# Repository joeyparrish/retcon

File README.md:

# Retro Console Controller

Use comfortable wireless PS3 controllers on your old Sega or Nintendo system.

> :warning: **NOTE** :warning:: _**This project has been deprecated.**_
> 
> I bought receivers from 8bitdo that do much more than my homebrew project ever could, in a smaller space, for less money.
> For example, here you can get a Sega Genesis receiver for bluetooth controllers that is tiny and powered by the Sega itself: https://www.8bitdo.com/retro-receiver-genesis-mega-drive/
> 
> I had begun a redesign based on a microcontroller that I hoped would be powered by the console itself, and would use generic Bluetooth instead of PS3, but for $20 (as of Feb 2024) it's hard to beat what 8bitdo is doing.
> 
> Feel free to build off of this repo if you wish, but I'm abandoning it in favor of https://www.8bitdo.com/
> 
> -Joey

-----

The PS3 controllers pair with a Raspberry Pi, which translates the controller
inputs to the game console through an external circuit.

[The repository][] hosts the schematics, board layouts, and source code.

For a list of known issues, see our [issue tracker][].

[The repository]: https://github.com/cashpipeplusplus/retcon
[issue tracker]: https://github.com/cashpipeplusplus/retcon/issues

## Software

RetCon consists of three pieces of software that run on a Raspberry Pi:

 * retcon - reads events from the gamepad and toggle GPIO pins
 * trusting-steed - waits for gamepads and marks them as "trusted"
 * sixpair - waits for PS3 controllers over USB and pairs them for bluetooth

These run on the Raspberry Pi, and I do not recommend cross-compiling them.
To build them, check out the source on Raspbian, install the deps, then build
the debian package:

```sh
git clone https://github.com/cashpipeplusplus/retcon
sudo apt-get install libusb-dev pigpio python-gobject python-dbus
cd retcon/src/
fakeroot ./debian/rules binary
```

To install on Raspbian:

```sh
sudo dpkg -i ../retcon_0.0.1-1_armhf.deb
```

## Raspberry Pi SD card image

The SD card image is generated using a fork of a tool called pi-gen, which is
included as a submodule.

From retcon, you can check out the pi-gen code like this:

```sh
git submodule update --init --recursive
```

To build the SD image, first you must build the retcon debian package from
Raspbian.  Then, copy the deb file to your Linux machine and build the SD image
there.  Assuming the deb file is in the retcon folder, run this:

```sh
cd pi-gen
sudo ./build.sh ../retcon_0.0.1-1_armhf.deb
```

The output will appear in `deploy/`.

## Pre-built SD card image

Pre-built SD card images are available from the [releases][] page.

[releases]: https://github.com/cashpipeplusplus/retcon/releases

## Hardware

The Raspberry Pi communicates with the game console through an external
circuit.  Schematics and board layouts for this extra hardware can be found
in the `circuit/` folder.  The board file can be uploaded directly to
[DirtyPCBs][] if you want the boards printed for you.  More details can be
found in `circuit/README.md`.

[DirtyPCBs]: http://dirtypcbs.com/

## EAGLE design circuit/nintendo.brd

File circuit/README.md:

These are the schematic and board files for the external circuit part of the
project.  This circuit is driven by the Raspberry Pi and translates GPIO pins
to the game console.

These files were created with the free version of [Eagle][] v7.7.0.

 - sega.sch (Eagle Schematic)
 - sega.sch.1.png (screenshot of the schematic)
 - sega.sch.2.png (screenshot of the schematic)
 - sega.brd (Eagle Board)
 - sega.brd.png (screenshot of the board)

The board file can be uploaded directly to [DirtyPCBs][] to be printed.

[Eagle]: https://cadsoft.io/
[DirtyPCBs]: http://dirtypcbs.com/

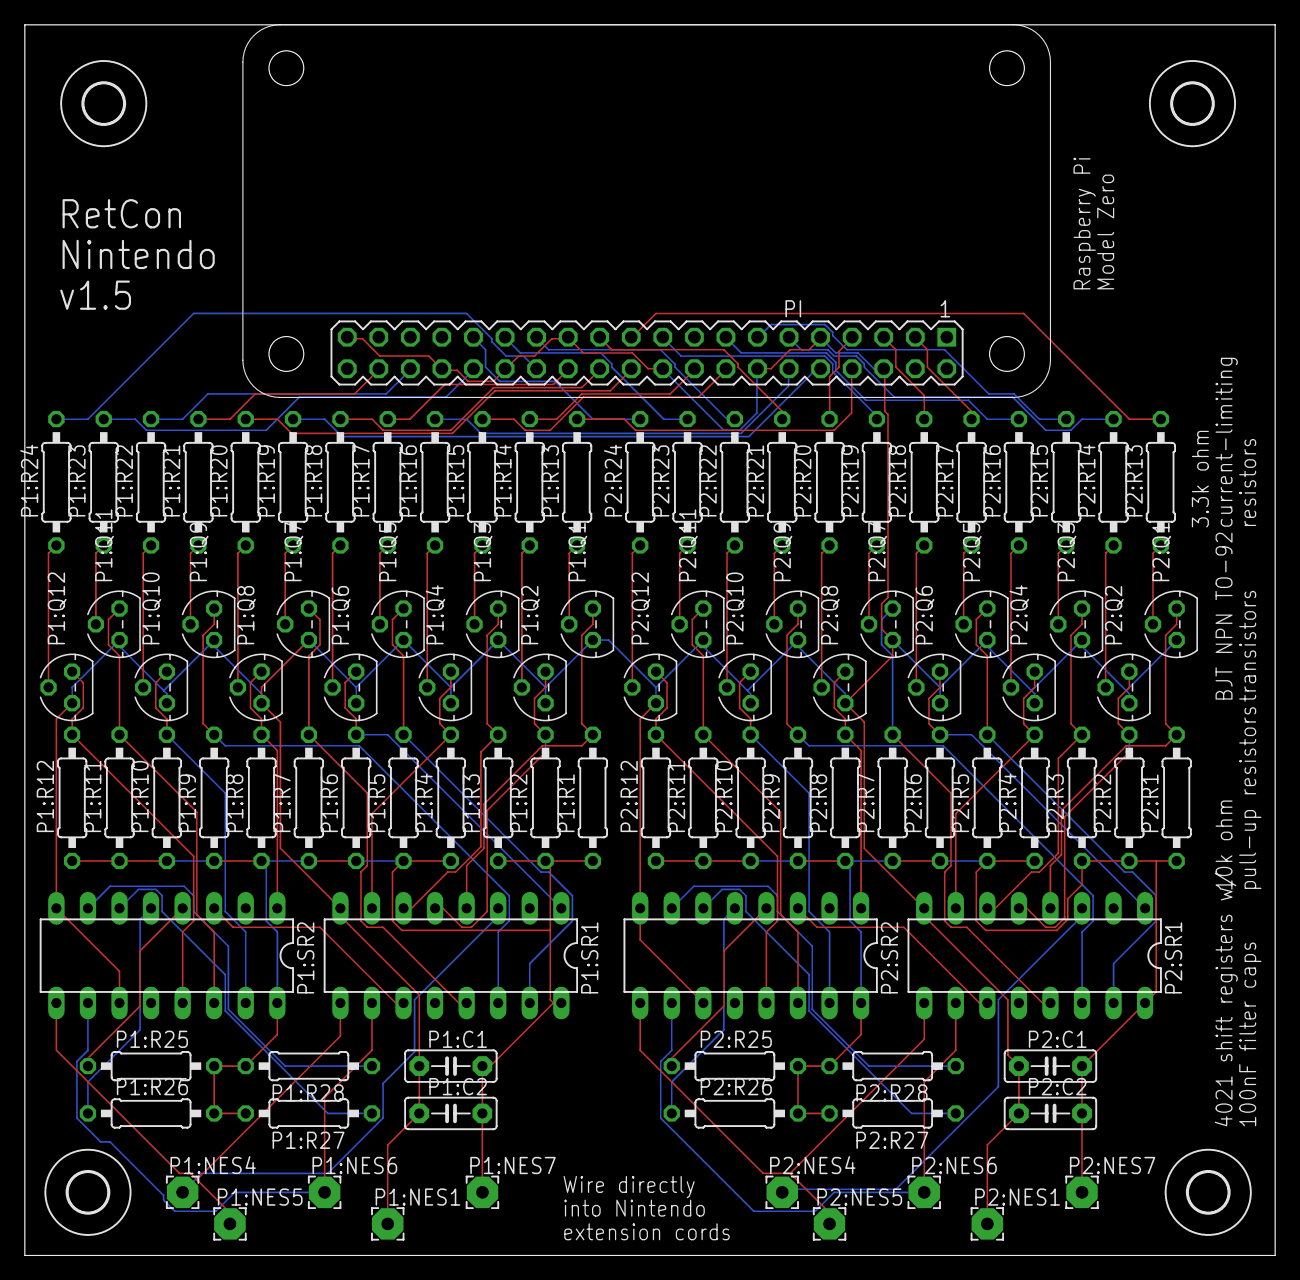
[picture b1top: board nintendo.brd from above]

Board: 2 copper layers, 100.6 x 99.0 mm, 103 parts (0 on the bottom side), 91 nets.

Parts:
P1:C1, P1:C2, P2:C1, P2:C2: 100nF; C5B2.5
P1:NES1, P1:NES4, P1:NES5, P1:NES6, P1:NES7, P2:NES1, P2:NES4, P2:NES5, P2:NES6, P2:NES7: -; 2,54/1,0
P1:Q1, P1:Q2, P1:Q3, P1:Q4, P1:Q5, P1:Q6, P1:Q7, P1:Q8, P1:Q9, P1:Q10, P1:Q11, P1:Q12, P2:Q1, P2:Q2, P2:Q3, P2:Q4, P2:Q5, P2:Q6, P2:Q7, P2:Q8, P2:Q9, P2:Q10, P2:Q11, P2:Q12: 2N3904; TO92
P1:R1, P1:R2, P1:R3, P1:R4, P1:R5, P1:R6, P1:R7, P1:R8, P1:R9, P1:R10, P1:R11, P1:R12, P1:R25, P1:R26, P1:R27, P1:R28, P2:R1, P2:R2, P2:R3, P2:R4, P2:R5, P2:R6, P2:R7, P2:R8, P2:R9, P2:R10, P2:R11, P2:R12, P2:R25, P2:R26, P2:R27, P2:R28: 10k; 0207/10
P1:R13, P1:R14, P1:R15, P1:R16, P1:R17, P1:R18, P1:R19, P1:R20, P1:R21, P1:R22, P1:R23, P1:R24, P2:R13, P2:R14, P2:R15, P2:R16, P2:R17, P2:R18, P2:R19, P2:R20, P2:R21, P2:R22, P2:R23, P2:R24: 3.3k; 0207/10
P1:SR1, P1:SR2, P2:SR1, P2:SR2: 4021N; DIL16
PI: PIZERO_THROUGH_HOLE; PIZERO_THOUGH_HOLE
U$1, U$2, U$3, U$4: 3,2

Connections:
unnamed: P2:R14.2, PI.11
unnamed: P1:C1.1, P1:C2.1, P1:NES1.1, P1:Q1.3, P1:Q2.3, P1:Q3.3, P1:Q4.3, P1:Q5.3, P1:Q6.3, P1:Q7.3, P1:Q8.3, P1:Q9.3, P1:Q10.3, P1:Q11.3, P1:Q12.3, P1:SR1.8, P1:SR2.8, P1:SR2.11, P2:C1.1, P2:C2.1, P2:NES1.1, P2:Q1.3, P2:Q2.3, P2:Q3.3, P2:Q4.3, P2:Q5.3, P2:Q6.3, P2:Q7.3, P2:Q8.3, P2:Q9.3, P2:Q10.3, P2:Q11.3, P2:Q12.3, P2:SR1.8, P2:SR2.8, P2:SR2.11, PI.6, PI.9, PI.14, PI.20, PI.25, PI.30, PI.34, PI.39
unnamed: P2:R15.2, PI.13
unnamed: P2:R17.2, PI.3
unnamed: P2:R18.2, PI.5
unnamed: P2:R20.2, PI.7
unnamed: P2:R16.2, PI.15
unnamed: P2:R19.2, PI.19
unnamed: P2:R13.2, PI.21
unnamed: P1:R13.2, PI.8
unnamed: P1:R19.2, PI.10
unnamed: P1:R16.2, PI.12
unnamed: P1:R15.2, PI.16
unnamed: P1:R14.2, PI.18
unnamed: P1:R20.2, PI.22
unnamed: P1:R18.2, PI.24
unnamed: P1:R17.2, PI.26
unnamed: P2:R21.2, PI.23
unnamed: P2:R22.2, PI.27
unnamed: P2:R23.2, PI.29
unnamed: P2:R24.2, PI.31
unnamed: P1:R21.2, PI.38
unnamed: P1:R22.2, PI.36
unnamed: P1:R23.2, PI.32
unnamed: P1:R24.2, PI.28
P1:A: P1:Q5.1, P1:R5.2, P1:SR1.15
P1:B: P1:Q6.1, P1:R6.2, P1:SR1.1
P1:C: P1:Q8.1, P1:R8.2, P1:SR2.1
P1:CLK: P1:NES6.1, P1:SR1.10, P1:SR2.10
P1:D: P1:Q2.1, P1:R2.2, P1:SR1.5
P1:L: P1:Q3.1, P1:R3.2, P1:SR1.6
P1:LATCH: P1:NES5.1, P1:SR1.9, P1:SR2.9
P1:N$1: P1:Q9.2, P1:R21.1
P1:N$2: P1:Q1.2, P1:R13.1
P1:N$3: P1:Q10.2, P1:R22.1
P1:N$4: P1:Q11.2, P1:R23.1
P1:N$5: P1:Q12.2, P1:R24.1
P1:N$9: P1:Q2.2, P1:R14.1
P1:N$10: P1:Q3.2, P1:R15.1
P1:N$11: P1:Q4.2, P1:R16.1
P1:N$12: P1:Q5.2, P1:R17.1
P1:N$13: P1:Q6.2, P1:R18.1
P1:N$14: P1:Q7.2, P1:R19.1
P1:N$15: P1:Q8.2, P1:R20.1
P1:N$19: P1:SR1.11, P1:SR2.3
P1:N$20: P1:R25.1, P1:SR2.4
P1:N$21: P1:R26.1, P1:SR2.5
P1:N$22: P1:R27.1, P1:SR2.6
P1:N$23: P1:R28.1, P1:SR2.7
P1:OUT: P1:NES4.1, P1:SR1.3
P1:R: P1:Q4.1, P1:R4.2, P1:SR1.7
P1:SL: P1:Q9.1, P1:R9.2, P1:SR1.14
P1:ST: P1:Q7.1, P1:R7.2, P1:SR1.13
P1:TL: P1:Q11.1, P1:R11.2, P1:SR2.14
P1:TR: P1:Q12.1, P1:R12.2, P1:SR2.13
P1:U: P1:Q1.1, P1:R1.2, P1:SR1.4
P1:VCC: P1:C1.2, P1:C2.2, P1:NES7.1, P1:R1.1, P1:R2.1, P1:R3.1, P1:R4.1, P1:R5.1, P1:R6.1, P1:R7.1, P1:R8.1, P1:R9.1, P1:R10.1, P1:R11.1, P1:R12.1, P1:R25.2, P1:R26.2, P1:R27.2, P1:R28.2, P1:SR1.16, P1:SR2.16
P1:X: P1:Q10.1, P1:R10.2, P1:SR2.15
P2:A: P2:Q5.1, P2:R5.2, P2:SR1.15
P2:B: P2:Q6.1, P2:R6.2, P2:SR1.1
P2:C: P2:Q8.1, P2:R8.2, P2:SR2.1
P2:CLK: P2:NES6.1, P2:SR1.10, P2:SR2.10
P2:D: P2:Q2.1, P2:R2.2, P2:SR1.5
P2:L: P2:Q3.1, P2:R3.2, P2:SR1.6
P2:LATCH: P2:NES5.1, P2:SR1.9, P2:SR2.9
P2:N$1: P2:Q9.2, P2:R21.1
P2:N$2: P2:Q1.2, P2:R13.1
P2:N$3: P2:Q10.2, P2:R22.1
P2:N$4: P2:Q11.2, P2:R23.1
P2:N$5: P2:Q12.2, P2:R24.1
P2:N$9: P2:Q2.2, P2:R14.1
P2:N$10: P2:Q3.2, P2:R15.1
P2:N$11: P2:Q4.2, P2:R16.1
P2:N$12: P2:Q5.2, P2:R17.1
P2:N$13: P2:Q6.2, P2:R18.1
P2:N$14: P2:Q7.2, P2:R19.1
P2:N$15: P2:Q8.2, P2:R20.1
P2:N$19: P2:SR1.11, P2:SR2.3
P2:N$20: P2:R25.1, P2:SR2.4
P2:N$21: P2:R26.1, P2:SR2.5
P2:N$22: P2:R27.1, P2:SR2.6
P2:N$23: P2:R28.1, P2:SR2.7
P2:OUT: P2:NES4.1, P2:SR1.3
P2:R: P2:Q4.1, P2:R4.2, P2:SR1.7
P2:SL: P2:Q9.1, P2:R9.2, P2:SR1.14
P2:ST: P2:Q7.1, P2:R7.2, P2:SR1.13
P2:TL: P2:Q11.1, P2:R11.2, P2:SR2.14
P2:TR: P2:Q12.1, P2:R12.2, P2:SR2.13
P2:U: P2:Q1.1, P2:R1.2, P2:SR1.4
P2:VCC: P2:C1.2, P2:C2.2, P2:NES7.1, P2:R1.1, P2:R2.1, P2:R3.1, P2:R4.1, P2:R5.1, P2:R6.1, P2:R7.1, P2:R8.1, P2:R9.1, P2:R10.1, P2:R11.1, P2:R12.1, P2:R25.2, P2:R26.2, P2:R27.2, P2:R28.2, P2:SR1.16, P2:SR2.16
P2:X: P2:Q10.1, P2:R10.2, P2:SR2.15

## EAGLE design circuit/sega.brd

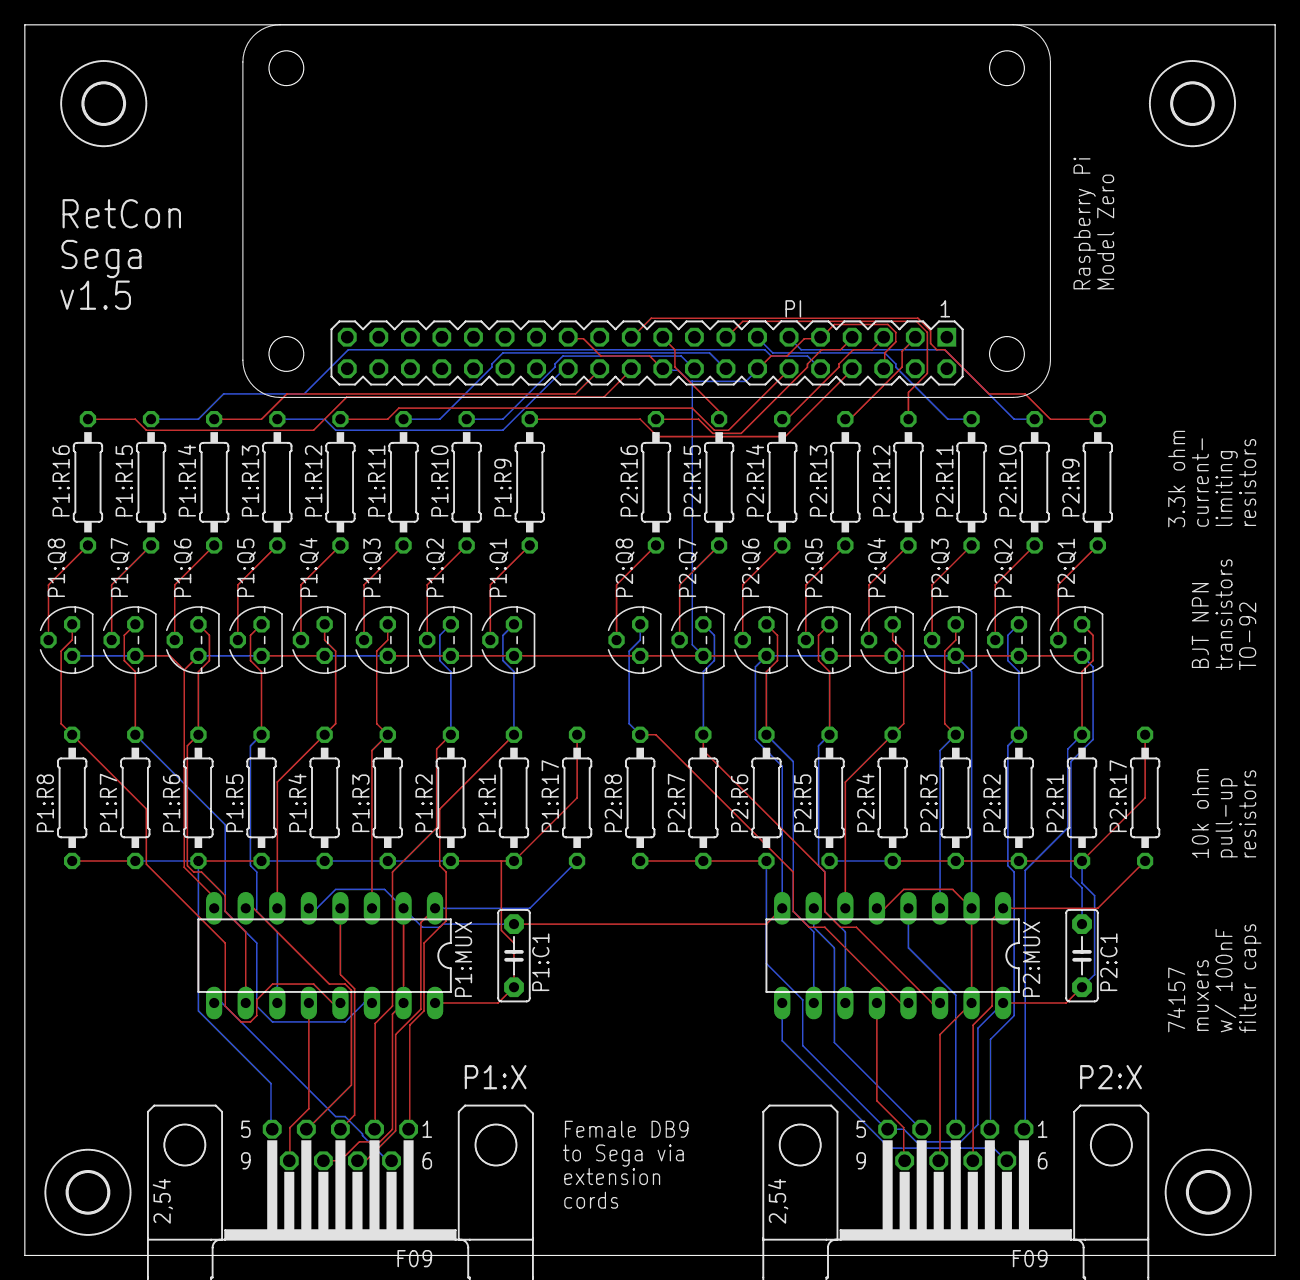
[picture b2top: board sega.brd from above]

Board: 2 copper layers, 100.6 x 99.0 mm, 61 parts (0 on the bottom side), 61 nets.

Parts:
P1:C1, P2:C1: 100nF; C5B2.5
P1:MUX, P2:MUX: 74LS157N; DIL16
P1:Q1, P1:Q2, P1:Q3, P1:Q4, P1:Q5, P1:Q6, P1:Q7, P1:Q8, P2:Q1, P2:Q2, P2:Q3, P2:Q4, P2:Q5, P2:Q6, P2:Q7, P2:Q8: 2N3904; TO92
P1:R1, P1:R2, P1:R3, P1:R4, P1:R5, P1:R6, P1:R7, P1:R8, P1:R17, P2:R1, P2:R2, P2:R3, P2:R4, P2:R5, P2:R6, P2:R7, P2:R8, P2:R17: 10k; 0207/10
P1:R9, P1:R10, P1:R11, P1:R12, P1:R13, P1:R14, P1:R15, P1:R16, P2:R9, P2:R10, P2:R11, P2:R12, P2:R13, P2:R14, P2:R15, P2:R16: 3.3k; 0207/10
P1:X, P2:X: -; F09H
PI: PIZERO_THROUGH_HOLE; PIZERO_THOUGH_HOLE
U$1, U$2, U$3, U$4: 3,2

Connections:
GND: P1:C1.1, P1:MUX.2, P1:MUX.5, P1:MUX.8, P1:MUX.15, P1:Q1.3, P1:Q2.3, P1:Q3.3, P1:Q4.3, P1:Q5.3, P1:Q6.3, P1:Q7.3, P1:Q8.3, P1:X.8, P2:C1.1, P2:MUX.2, P2:MUX.5, P2:MUX.8, P2:MUX.15, P2:Q1.3, P2:Q2.3, P2:Q3.3, P2:Q4.3, P2:Q5.3, P2:Q6.3, P2:Q7.3, P2:Q8.3, P2:X.8, PI.6, PI.9, PI.14, PI.20, PI.25
unnamed: P2:R10.2, PI.11
unnamed: P2:R11.2, PI.13
unnamed: P2:R13.2, PI.3
unnamed: P2:R14.2, PI.5
unnamed: P2:R16.2, PI.7
unnamed: P2:R12.2, PI.15
unnamed: P2:R15.2, PI.19
unnamed: P2:R9.2, PI.21
unnamed: P1:R9.2, PI.8
unnamed: P1:R15.2, PI.10
unnamed: P1:R12.2, PI.12
unnamed: P1:R11.2, PI.16
unnamed: P1:R10.2, PI.18
unnamed: P1:R16.2, PI.22
unnamed: P1:R14.2, PI.24
unnamed: P1:R13.2, PI.26
P1:A: P1:MUX.11, P1:Q5.1, P1:R5.2
P1:A|B: P1:MUX.9, P1:X.6
P1:B: P1:MUX.10, P1:Q6.1, P1:R6.2
P1:C: P1:MUX.13, P1:Q8.1, P1:R8.2
P1:D: P1:Q2.1, P1:R2.2, P1:X.2
P1:G|L: P1:MUX.4, P1:X.3
P1:G|R: P1:MUX.7, P1:X.4
P1:L: P1:MUX.3, P1:Q3.1, P1:R3.2
P1:N$2: P1:Q1.2, P1:R9.1
P1:N$9: P1:Q2.2, P1:R10.1
P1:N$10: P1:Q3.2, P1:R11.1
P1:N$11: P1:Q4.2, P1:R12.1
P1:N$12: P1:Q5.2, P1:R13.1
P1:N$13: P1:Q6.2, P1:R14.1
P1:N$14: P1:Q7.2, P1:R15.1
P1:N$15: P1:Q8.2, P1:R16.1
P1:R: P1:MUX.6, P1:Q4.1, P1:R4.2
P1:S: P1:MUX.14, P1:Q7.1, P1:R7.2
P1:SEL: P1:MUX.1, P1:R17.1, P1:X.7
P1:S|C: P1:MUX.12, P1:X.9
P1:U: P1:Q1.1, P1:R1.2, P1:X.1
P1:VCC: P1:C1.2, P1:MUX.16, P1:R1.1, P1:R2.1, P1:R3.1, P1:R4.1, P1:R5.1, P1:R6.1, P1:R7.1, P1:R8.1, P1:R17.2, P1:X.5
P2:A: P2:MUX.11, P2:Q5.1, P2:R5.2
P2:A|B: P2:MUX.9, P2:X.6
P2:B: P2:MUX.10, P2:Q6.1, P2:R6.2
P2:C: P2:MUX.13, P2:Q8.1, P2:R8.2
P2:D: P2:Q2.1, P2:R2.2, P2:X.2
P2:G|L: P2:MUX.4, P2:X.3
P2:G|R: P2:MUX.7, P2:X.4
P2:L: P2:MUX.3, P2:Q3.1, P2:R3.2
P2:N$2: P2:Q1.2, P2:R9.1
P2:N$9: P2:Q2.2, P2:R10.1
P2:N$10: P2:Q3.2, P2:R11.1
P2:N$11: P2:Q4.2, P2:R12.1
P2:N$12: P2:Q5.2, P2:R13.1
P2:N$13: P2:Q6.2, P2:R14.1
P2:N$14: P2:Q7.2, P2:R15.1
P2:N$15: P2:Q8.2, P2:R16.1
P2:R: P2:MUX.6, P2:Q4.1, P2:R4.2
P2:S: P2:MUX.14, P2:Q7.1, P2:R7.2
P2:SEL: P2:MUX.1, P2:R17.1, P2:X.7
P2:S|C: P2:MUX.12, P2:X.9
P2:U: P2:Q1.1, P2:R1.2, P2:X.1
P2:VCC: P2:C1.2, P2:MUX.16, P2:R1.1, P2:R2.1, P2:R3.1, P2:R4.1, P2:R5.1, P2:R6.1, P2:R7.1, P2:R8.1, P2:R17.2, P2:X.5

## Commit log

2016-10-29 Rename the project.
2016-10-29 Import controller source code
    Closes #1
2016-10-29 Clean up controller source and add comments
2016-10-29 Add build system for controller app
    Closes #2
2016-10-29 Add clean to controller Makefile
2016-11-04 Add sixpair
2016-11-04 Rename controller to retcon
2016-11-04 Add debian package metadata
2016-11-04 Add schematic and board for circuit v1.1
    Closes #6
2016-11-04 Update circuit design to v1.2
    - Raspberry Pi Zero mounted directly to the board replaces header
    - DB9 connectors replace individual jumper wires to the controller
2016-11-05 Add missing pull-up resistor to circuit
    A pull-up was missing on the select pin.
2016-11-05 Add trusting-steed to trust all gamepads
    Closes #9
2016-11-05 Update READMEs
    Consolidates src/README.md with README.md, updates build instructions.
2016-11-05 Add pi-gen fork as submodule
2016-11-05 Update pi-gen
2016-11-05 Hide value layer and add more pngs
    This layer is ignored by DirtyPCBs, so the board in Eagle is now more
    representative of the final hardware. Also adds PNGs of the board and
    every part of the schematic.
2016-11-05 Finish the basic build docs
    Closes #10
2016-11-05 Add missing pigpio dep
    For some reason, the debian build scripts do not add this dep for me
    based on dynamic libs.
2016-11-05 Fix init script name for trusting-steed
2016-11-05 Fix package build failure
    The package started failing to build when I removed src/README.md
2016-11-05 Clean up init scripts, fix retcon startup issues
    Issue #13
2016-11-05 Update pi-gen
    Closes #13
2016-11-06 Add controller interface docs for Sega
    Issue #8
2016-11-06 Resize Sega interface doc images
    The images were too large, but it was difficult to know until I could
    see the markdown rendered on github.
    Issue #8
2016-11-06 Add external references for Sega interface docs
    Issue #8
2016-11-12 Add NES and SNES controller docs
    Closes #8
2016-11-15 Add explicit junctions to the schematic
2016-11-30 Boot in read-only mode
    Closes #12
2016-11-30 Reduce the image size
    v1.2.0 was 1.4GB uncompressed and 292MB zipped.
    With this, the image is now 533MB uncompressed and 162MB zipped.
    Closes #16
2016-12-01 RetCon image can now be used to compile RetCon
    Closes #15
2016-12-06 Fix trusting-steed shutdown
    Because trusting-steed is a python script, the executable name is
    python, not trusting-steed. Using the --name argument to
    start-stop-daemon means it will check the executable name and only
    stop the application if it matches. Therefore we have to remove the
    --name argument to fix shutdown of the service.
    Closes #17
2016-12-06 Fix swapped pins in sega interface docs
    Pin 5 is VCC, pin 7 is select. Whoops.
2016-12-06 Add logo
2017-05-05 Fix Sega DB9 placement
    These connectors were too far from the edge of the board, and it made
    it very difficult to connect the extension cord. I had to modify the
    cord to get v1.2 working. This fixes the placement and updates the
    version number to v1.3.
2017-05-05 Replace optocouplers with transistors
    This makes the board cheaper and frees up some space for additional
    hardware in future revisions. This is hardware v1.4.
2017-05-18 Document button mappings
    This includes mappings for Nintendo systems, even though this has not
    been implemented yet.
2017-05-18 Fix button mapping doc
    I left out a cell in the table before.
    This also adds a footnote explaining why there is a duplicate row.
2017-05-18 Factor pin mappings out of button mapping table
2017-06-19 Fix Sega board, v1.5
    - Fix pin names and directions
    - Fix missing connections to GND
    - Add missing junctions to the schematic
    Closes #19
2017-06-19 Update button mappings to include Nintendo outputs
    Issue #7
2017-06-19 Add Nintendo circuit, v1.5
    Should work with either NES or SNES.
    Closes #7
2019-02-27 Add docs on wire colors in Nintendo extension cords
2019-02-27 Correct SNES serial bits docs
    There are 16 bits clocked out, even though only 12 are used.
2024-02-06 Deprecate the project
